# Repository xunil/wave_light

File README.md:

# Wave light LED interface board
Simple board with connectors and resistors for LEDs which light the arms of a kinetic sculpture light.

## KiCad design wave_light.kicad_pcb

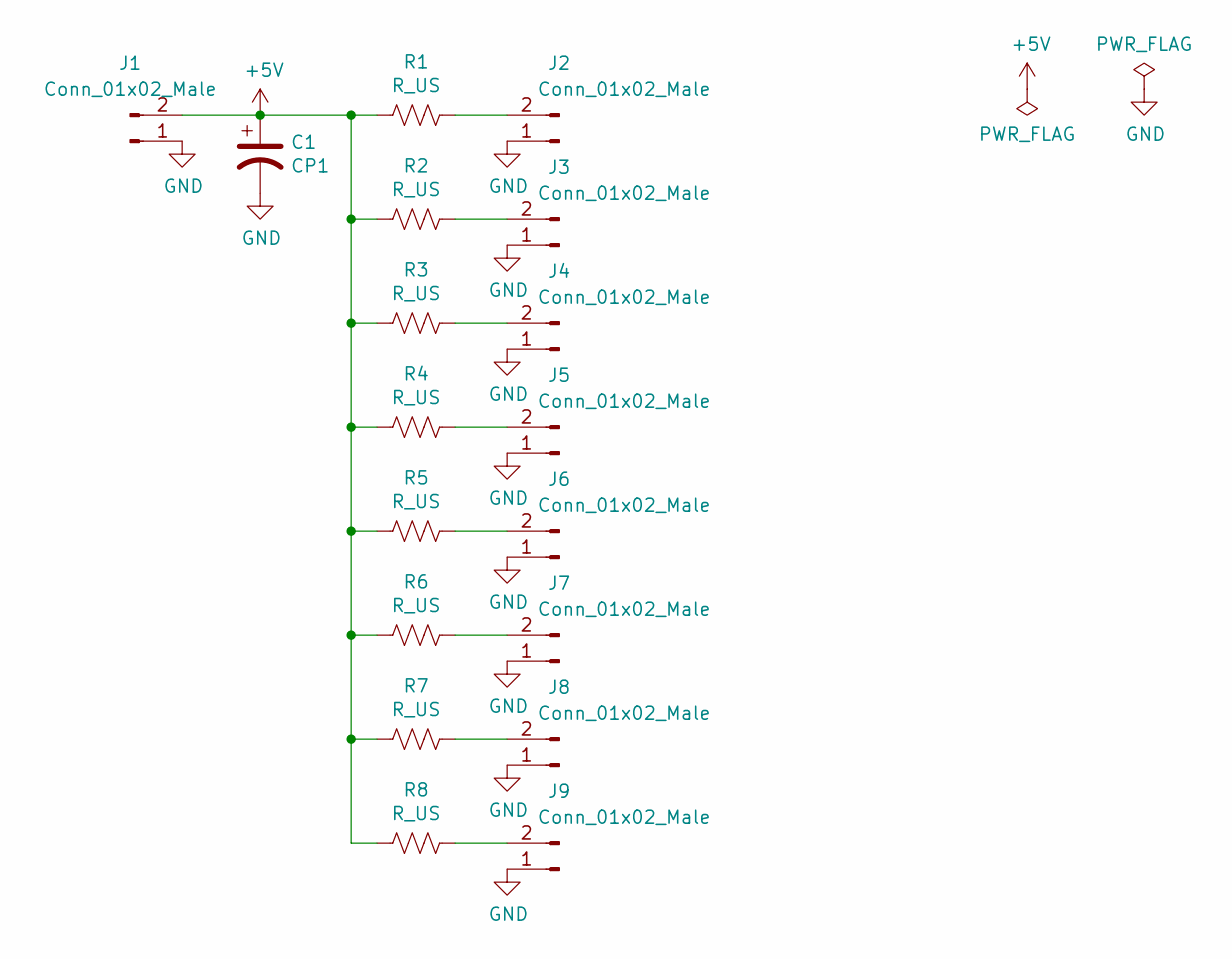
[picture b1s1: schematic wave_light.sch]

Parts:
C1: CP1; C_1206_3216Metric_Pad1.42x1.75mm_HandSolder
J1, J2, J3, J4, J5, J6, J7, J8, J9: Conn_01x02_Male; JST_XH_B2B-XH-A_1x02_P2.50mm_Vertical
R1, R2, R3, R4, R5, R6, R7, R8: R_US; R_1206_3216Metric_Pad1.42x1.75mm_HandSolder

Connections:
+5V: C1.1, J1.2, R1.2, R2.2, R3.2, R4.2, R5.2, R6.2, R7.2, R8.2
GND: C1.2, J1.1, J2.1, J3.1, J4.1, J5.1, J6.1, J7.1, J8.1, J9.1
unnamed: J2.2, R1.1
unnamed: J3.2, R2.1
unnamed: J4.2, R3.1
unnamed: J5.2, R4.1
unnamed: J6.2, R5.1
unnamed: J7.2, R6.1
unnamed: J8.2, R7.1
unnamed: J9.2, R8.1

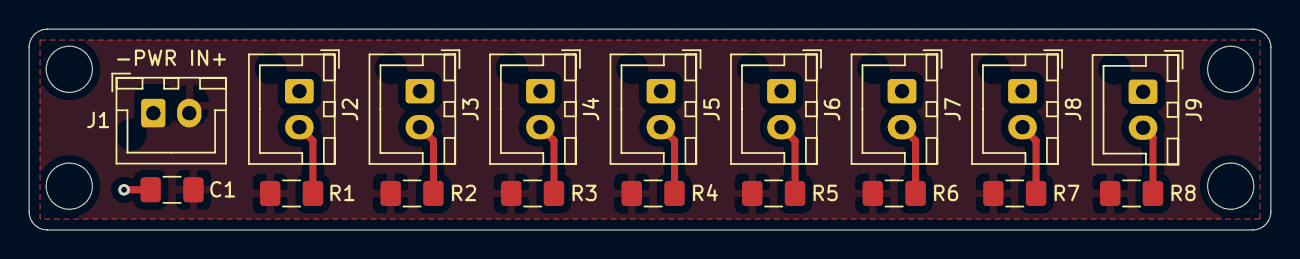
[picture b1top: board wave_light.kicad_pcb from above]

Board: 2 copper layers, 86.4 x 14.0 mm, 18 parts (0 on the bottom side), 10 nets.

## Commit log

2020-06-03 Initial import
2020-06-10 Redesign with rectangular layout
